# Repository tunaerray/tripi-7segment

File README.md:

# TRIPI 7-Segment Display Module

A peripheral expansion board designed for the TRIPI (Trion-based FPGA) platform, featuring 8 seven-segment displays, external push buttons, switches, and a reset mechanism.

## Overview

This project provides a ready-to-use hardware module for FPGA-based digital logic and display control applications. The board connects directly to the 40-pin GPIO header of the TRIPI FPGA board, enabling students and developers to implement and test digital systems without additional wiring or breadboarding.

## Features

- 8x seven-segment displays for multi-digit numeric output
- External push buttons and switches for user input
- Reset functionality for system control
- 2-layer PCB designed for the TRIPI FPGA 40-pin GPIO header
- Plug-and-play integration with the Trion-based FPGA platform

## Use Case

Designed as an educational hardware platform, this module allows students to:

- Implement digital logic circuits on a real FPGA
- Develop display control and multiplexing applications
- Prototype FPGA-based digital systems
- Learn hardware-software co-design in an embedded context

## Hardware

- **Platform:** TRIPI (Trion-based FPGA)
- **Interface:** 40-pin GPIO header
- **PCB:** 2-layer board
- **Display:** 8x seven-segment displays
- **Input:** Push buttons, DIP switches, reset button

## Images

### PCB Front

### PCB Back

.

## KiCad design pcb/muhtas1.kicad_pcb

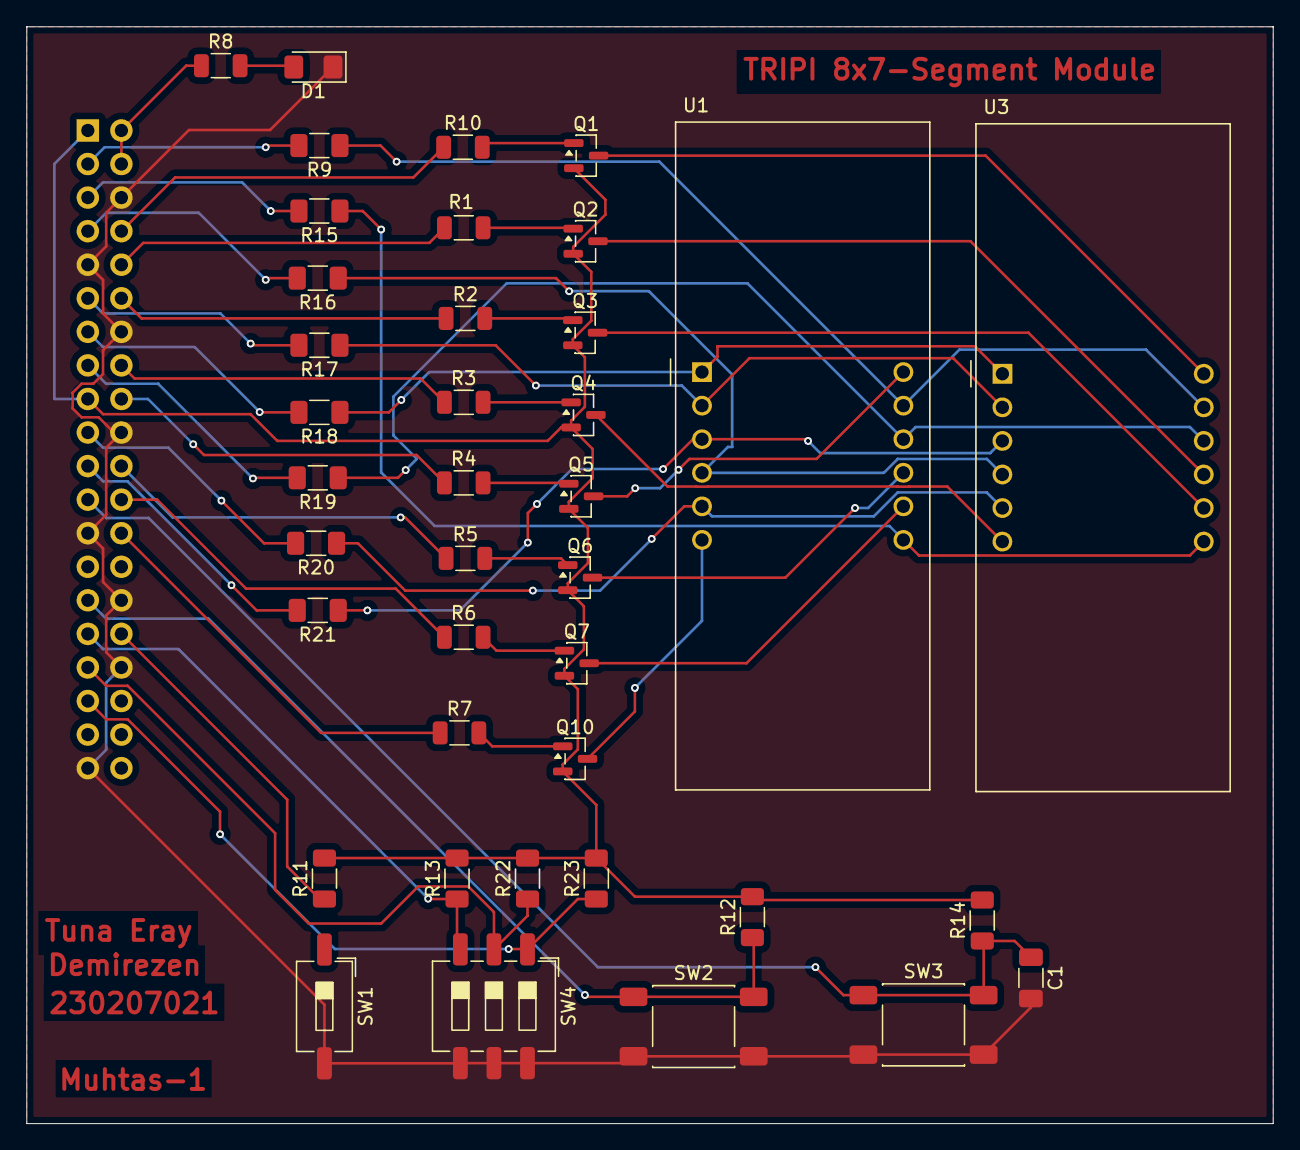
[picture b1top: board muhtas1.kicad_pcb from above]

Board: 2 copper layers, 94.3 x 83.0 mm, 40 parts (1 on the bottom side), 50 nets.

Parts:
C1: 100nF; C_1206_3216Metric_Pad1.33x1.80mm_HandSolder
D1: LED; LED_1206_3216Metric_Pad1.42x1.75mm_HandSolder
J2: Conn_02x20_Odd_Even; PinSocket_2x20_P2.54mm_Vertical
Q1, Q2, Q3, Q4, Q5, Q6, Q7, Q10: MMBTA56; SOT-23
R1, R2, R3, R4, R5, R6, R7, R8, R10: 2.2kR; R_1206_3216Metric
R9, R15, R16, R17, R18, R19, R20, R21: 330R; R_1206_3216Metric_Pad1.30x1.75mm_HandSolder
R11, R12, R13, R14, R22, R23: 10K; R_1206_3216Metric_Pad1.30x1.75mm_HandSolder
SW1: SW_DIP_x01; SW_DIP_SPSTx01_Slide_6.7x4.1mm_W8.61mm_P2.54mm_LowProfile
SW2, SW3: SW_Push; SW_Push_1P1T_NO_E-Switch_TL3301NxxxxxG
SW4: SW_DIP_x03; SW_DIP_SPSTx03_Slide_6.7x9.18mm_W8.61mm_P2.54mm_LowProfile
U1, U3: CA56-12SEKWA

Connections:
+3.3V: J2.1, J2.17, Q1.2 (E), Q2.2 (E), Q3.2 (E), Q4.2 (E), Q5.2 (E), Q6.2 (E), Q7.2 (E), Q10.2 (E), R11.2, R12.2, R13.2, R14.2, R22.2, R23.2
+5V: J2.2, J2.4, R8.1
CA1: J2.8, R10.1
CA2: J2.10, R1.1
CA3: J2.12, R2.1
CA4: J2.16, R3.1
CA5: J2.18, R4.1
CA6: J2.22, R5.1
CA7: J2.24, R6.1
CA8: J2.26, R7.1
DEBUG: J2.29, R12.1, SW2.1
GND: C1.2, D1.1 (K), J2.6, J2.9, J2.14, J2.20, J2.25, J2.30, J2.34, J2.39, SW1.2, SW2.2, SW3.2, SW4.4, SW4.5, SW4.6
MODE: J2.32, R11.1, SW1.1
unnamed: D1.2 (A), R8.2
unnamed: Q1.1 (B), R10.2
unnamed: Q1.3 (C), U3.12 (CA1)
unnamed: Q2.1 (B), R1.2
unnamed: Q2.3 (C), U3.9 (CA2)
unnamed: Q3.1 (B), R2.2
unnamed: Q3.3 (C), U3.8 (CA3)
unnamed: Q4.1 (B), R3.2
unnamed: Q4.3 (C), U3.6 (CA4)
unnamed: Q5.1 (B), R4.2
unnamed: Q5.3 (C), U1.12 (CA1)
unnamed: Q6.1 (B), R5.2
unnamed: Q6.3 (C), U1.9 (CA2)
unnamed: Q7.1 (B), R6.2
unnamed: Q7.3 (C), U1.8 (CA3)
unnamed: Q10.1 (B), R7.2
unnamed: Q10.3 (C), U1.6 (CA4)
unnamed: R21.1, U1.3 (DPX), U3.3 (DPX)
unnamed: R9.1, U1.11 (a), U3.11 (a)
unnamed: R15.1, U1.7 (b), U3.7 (b)
unnamed: R16.1, U1.4 (c), U3.4 (c)
unnamed: R17.1, U1.2 (d), U3.2 (d)
unnamed: R18.1, U1.1 (e), U3.1 (e)
unnamed: R19.1, U1.10 (f), U3.10 (f)
unnamed: R20.1, U1.5 (g), U3.5 (g)
RST: C1.1, J2.23, R14.1, SW3.1
a: J2.3, R9.2
b: J2.5, R15.2
bit1: J2.31, R13.1, SW4.3
bit2: J2.33, R22.1, SW4.2
bit3: J2.35, R23.1, SW4.1
c: J2.7, R16.2
d: J2.11, R17.2
dpx: J2.21, R21.2
e: J2.13, R18.2
f: J2.15, R19.2
g: J2.19, R20.2

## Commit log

2026-06-01 Revise README with features and use case details
